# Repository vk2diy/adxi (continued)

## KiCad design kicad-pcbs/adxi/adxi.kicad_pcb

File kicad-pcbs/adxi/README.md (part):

# adxi

## Timeline

 * Conceived: 2024-08-03
 * Designed: 2024-08-03 - 2024-10-10ish
 * Ordered: 2024-10-24
   * Cost: $41.40 for 10 boards + $154.20 for 10 pieces SMT = $195.60 for 10 pieces / 10 = $19.56 each (ex shipping)
   * Note that the ordering was delayed for 2 weeks or something owing to the late stage module design needing revision and wanting to share shipping costs, and this required updates to the [classe2-calculator](https://github.com/vk2diy/classe2-calculator) software.
 * ETA: 2024-11-06 
 * Received: 2024-11-04 (~midday) - total time since ordering ~10-11 days
 * Testing:
   * 2024-11-04: Blew up two boards, discovered USB power issue.
   * 2024-11-05: USB hub, audio and MCU passthru verified with bypass supply. Restored lab to functionality. Worked on a fix, ordered parts.
   * 2024-11-06: Parts received. Testing done manually powering the `TUSB321` chipset and negotiation appears to occur. This suggests a fixable situation. The boost converter still needs debugging.
   * 2024-11-07: Boost converter block instrumentation and testing.
   * 2024-11-08: Plan for potential power stage resolution patch board, scheme for early stage power and failover, benchtop regulator testing.
   * 2024-11-09: Irregular 'regulator free' early stage power solution, new board setup, prepare for firmware programming.
   * 2024-11-24: Test clock generator.

## Initial test

 * Visual inspection
   * No obvious defects
   * The silkscreen now appears to be printed with an inkjet and is much less clear than previous eras
 * Multimeter inspection
   * The GND net appears to be consistent across the board
   * None of the power nets short to GND
 * Assembly test
   * Hard to get the cable through the hole.
   * While easy to thread (dimensions are fine) I failed to account for the solid plug being in the way of the cable
 * Fiddly to tighten nylon nuts around standoffs

## Initial soldering

 * Found pins for MCU not easy to solder, maybe soldermask problem
 * Put one in backwards (oops!)
   * Result: First destroyed board. Nine remain.

## Issue #1: USB-C Power Distribution
 * Next board tried connecting USB-C to a powered USB2 hub just to probe board power
 * See some power on USBC = 0.xV and USBC CLEAN = 0.xV but nothing elsewhere, have to trace back using schematic.
 * Soldered some test leads on to the related test points
 * Configured oscilloscope to view these channels:
   * The scope shows 300mV for CH2 = USBC CLEAN and 500mV for CH1 = USBC
 * Both boards show this issue, which suggests a probable design problem
 * Test results for all three cases (backwards MCU on otherwise new board, no MCU on new board, correct orientation MCU on new board):
   * Test point '5V' = 0V
   * Test point 'USBC' = 500mV
   * Test point 'USBC CLEAN' = 300mV
   * Net 'USB-C-VBUS' = 5V
 * __Conclusion__
   * Design, configuration or placement problem regarding `TUSB321` chipset.
   * Chip is too small to probe directly. but pins are as follows:
     * CC1 = bidirectional USB PD channel
     * CC2 = bidirectional USB PD channel
     * ...
   * __Hypothesis__
     * I misunderstood the datasheet.
       * Instead of the chip relaying the power, which is obtained through the CC channels, it in fact requires a separate supply, which it was not given (and I was treating as an output).
       * Therefore, no power was being relayed to the rest of the board.
       * Additionally, the last page of the datasheet specifies that a 100nF bypass should be present at the VDD pin.
     * The good news is this should be possible to fix without a board revision by bringing VDD power from the 5V verified as present on the `USB-C-VBUS` net, after the ferrite bead.

 * __Attempted fix #1: Jumper cable__
   * Soldered a cable between the `USB-C-VBUS` output after the ferrite and the `USB-C-CLEAN` net (which connects to the `TUSB321` `VDD` pin.
   * __Hypothesis__
     * This should have taken 5V to the 5V clean output as input to the `TUSB321` boost converter, allowing it to negotiate more power.
   * __Result__
     * The `TUSB321` boost converter released magic smoke instantly.
     * Second destroyed board. Eight remain.
   * __Analysis__
     * IC orientation is visually verified as correct
     * Unsure why this occurred, in particular:
       * Given that 5V was measured
       * Given `TUSB321` is supposed to have thermal shutdown
       * Given `TUSB321` only has two inputs, the feedback pin and the main input pin, the latter receiving 5V only
       * Given that the feedback circuit had been modeled.
   * __Conclusion__
     * Design, configuration or placement issue within the `TUB321` circuit
   * __Potential next steps__
     * Use the first destroyed board where this section is intact to test the circuit more carefully using a bench supply and the oscilloscope.
       * This will rely on restoring the test equipment network which appears to be down right now.
       * Very short pulses of power or power with a current cutoff could be measured on the input, output and feedback pins to understand the behaviour without destroying the chip.
       * In the worst case, it should be possible to simply relegate this portion of the circuit to next edition and power the board through the 12V test point.
       * If it appears things are generally in order, then, to reduce inrush current, bulk capacitors could perhaps be disconnected.
     * Bypass the power stage with a direct supply

 * __Attempted bypass #1: Direct 12V supply__
   * Prepared an LXI network configurable power supply Rigol DP832 to connect to 12V test point and GND test point
     * Channel configuration is 12V with overvoltage protection enabled, and 0.05A with overcurrent protection enabled
   * A timed script will enable power for a short time so that the oscilloscope can capture the effect of the power on the other power rails (5V, 3.3V) which should come up.
     * The current limit will be iteratively increased slightly until bring-up succeeds.
     * If these come up, based on the MCU module's internal regulator, then we should be in business, and can move on to testing USB functionality.
     * We may also discover additional problems, although shorts have already been ruled out with multimeter-based continuity probing.
   * Before this test can proceed:
     * I had to debug some issues with my test network due to long period of disuse (network cable had been removed and replaced for another purpose)
     * I had to verify connectivity to the oscilloscope (for screenshot capability) and power supply (for control purposes)
     * It would be good to to first verify the script and control circuit with no load using the multimeter.
   * Configuration screenshot: 
   * Script output: 
```
Tue Nov  5 09:21:44 AM AEDT 2024
DP832 PSU
 - Status: OFF
 - Version: RIGOL TECHNOLOGIES,DP832,DP8C233203778,00.01.16
 - Self test: TopBoard:PASS,BottomBoard:PASS,Fan:PASS

Turning channels off... OK
Setting up channel #1
 - Voltage: 24.000V
 - Voltage limit: 24.000V
 - Voltage limiting: ON
 - Current: 0.500A
 - Current limit: 0.500A
 - Current limiting: ON
Setting up channel #2
 - Voltage: 12.000V
 - Voltage limit: 12.000V
 - Voltage limiting: ON
 - Current: 0.050A
 - Current limit: 0.050A
 - Current limiting: ON
Setting up channel #3
 - Voltage: 5.000V
 - Voltage limit: 5.000V
 - Voltage limiting: ON
 - Current: 0.500A
 - Current limiting: ON

Triggering channel 2 (12V) for test period
 - Enable
Saved screenshot_192.168.8.3_2024-11-05T09:21:44.png
 - Disable

Tue Nov  5 09:21:45 AM AEDT 2024
```

   * Analysis:
     * The screenshot showed no current consumption
     * Connections were therefore checked and an alligator clip was replaced with a soft solder tie-down to the test point
     * The script still ran without change, however re-enabling the channel manually resulted in an overcurrent alarm
     * The current was manually increased as follows: 0.1A, 0.2A
     * At 0.2A power-on occurs and the LED from the MCU can be seen, but this is not reliable.
     * At 0.3A reliability is attained 

```
Tue Nov  5 09:37:42 AM AEDT 2024
DP832 PSU
 - Status: OFF
 - Version: RIGOL TECHNOLOGIES,DP832,DP8C233203778,00.01.16
 - Self test: TopBoard:PASS,BottomBoard:PASS,Fan:PASS

Turning channels off... OK
Setting up channel #1
 - Voltage: 24.000V
 - Voltage limit: 24.000V
 - Voltage limiting: ON
 - Current: 0.500A
 - Current limit: 0.500A
 - Current limiting: ON
Setting up channel #2
 - Voltage: 12.000V
 - Voltage limit: 12.000V
 - Voltage limiting: ON
 - Current: 0.300A
 - Current limit: 0.300A
 - Current limiting: ON
Setting up channel #3
 - Voltage: 5.000V
 - Voltage limit: 5.000V
 - Voltage limiting: ON
 - Current: 0.500A
 - Current limiting: ON

Triggering channel 2 (12V) for test period
 - Enable
Saved screenshot_192.168.8.3_2024-11-05T09:37:43.png
 - Disable

Tue Nov  5 09:37:44 AM AEDT 2024
```

   * Conclusion:
     * Board is at least partly functional with MCU power-on detected
     * Additional channels of 5V and 3.3V also come up as follows  

## USB testing

Now that we have power, it may be possible to test USB connectivity.

Firstly we should take care before plugging in the USB to ensure that the USB VBUS does not burn anything else. The jumper lead that allowed this to burn the boost converter has been removed and the initial state (some minor voltage seen through `TUSB321` `VDD` pin presumably bleeding through from `VBUS_DET` via the large resistor) should be replicated. Since this is insufficient to enable `TUSB321` we should see it remain idle, and the subsequent power stage which burned, namely the jumpered input to the boost converter `MT3608B`, has been removed. Subsequent diodes should prevent further issue.

So the plan is:
 * Plug in USBC
 * See whether anything burns or gets hot
 * If not, then proceed to apply power.
 * After applying power, see if the USB hub comes up, USB audio chipset comes up, or the passthru to the MCU for serial control and programming over the shared USB-C line works.

Here we go... success! `dmesg` output showed the following.

```
[131935.240875] usb 5-4.3: new high-speed USB device number 9 using xhci_hcd
[131935.354394] usb 5-4.3: New USB device found, idVendor=1a40, idProduct=0101,
bcdDevice= 1.00
[131935.354397] usb 5-4.3: New USB device strings: Mfr=0, Product=1, SerialNumbe
r=0
[131935.354399] usb 5-4.3: Product: USB2.0 HUB
[131935.364516] hub 5-4.3:1.0: USB hub found
[131935.364585] hub 5-4.3:1.0: 4 ports detected
[131935.747540] usb 5-4.3.2: new full-speed USB device number 10 using xhci_hcd
[131936.021358] usb 5-4.3.2: New USB device found, idVendor=1a86, idProduct=7523
, bcdDevice= 2.54
[131936.021362] usb 5-4.3.2: New USB device strings: Mfr=0, Product=2, SerialNum
ber=0
[131936.021365] usb 5-4.3.2: Product: USB2.0-Ser!
[131936.360870] usb 5-4.3.1: new full-speed USB device number 11 using xhci_hcd
[131936.635396] usb 5-4.3.1: New USB device found, idVendor=0d8c, idProduct=0012
, bcdDevice= 1.00
[131936.635398] usb 5-4.3.1: New USB device strings: Mfr=1, Product=2, SerialNum
ber=0
[131936.635399] usb 5-4.3.1: Product: USB Audio Device
[131936.635400] usb 5-4.3.1: Manufacturer: C-Media Electronics Inc.
[131936.675747] input: C-Media Electronics Inc. USB Audio Device as /devices/pci
0000:00/0000:00:02.1/0000:03:00.0/0000:04:0c.0/0000:14:00.0/usb5/5-4/5-4.3/5-4.3
.1/5-4.3.1:1.3/0003:0D8C:0012.0009/input/input33
[131936.734251] hid-generic 0003:0D8C:0012.0009: input,hidraw8: USB HID v1.00 De
vice [C-Media Electronics Inc. USB Audio Device] on usb-0000:14:00.0-4.3.1/input
3
[131936.762002] usbcore: registered new interface driver usbserial_generic
[131936.762010] usbserial: USB Serial support registered for generic
[131936.766921] usbcore: registered new interface driver ch341
[131936.766929] usbserial: USB Serial support registered for ch341-uart
[131936.766937] ch341 5-4.3.2:1.0: ch341-uart converter detected
[131936.767494] ch341-uart ttyUSB0: break control not supported, using simulated
 break
[131936.767523] usb 5-4.3.2: ch341-uart converter now attached to ttyUSB0
[131937.067790] usb 5-4.3: USB disconnect, device number 9
[131937.067792] usb 5-4.3.1: USB disconnect, device number 11
[131937.137341] usb 5-4.3.2: USB disconnect, device number 10
[131937.137450] ch341-uart ttyUSB0: ch341-uart converter now disconnected from t
tyUSB0
[131937.137464] ch341 5-4.3.2:1.0: device disconnected
```

This tells us that:
 * USB data lines work both on the host-side and the board-side
 * The USB hub works
 * The audio chipset is detected
 * The USB cable passthru to the MCU module works
   * The CH341 serial UART on the MCU is detected

Fantastic! Let's power it on a bit longer to get a USB tree display.

```
        |__ Port 003: Dev 015, If 0, Class=Hub, Driver=hub/4p, 480M
            |__ Port 001: Dev 017, If 0, Class=Audio, Driver=snd-usb-audio, 12M
            |__ Port 001: Dev 017, If 1, Class=Audio, Driver=snd-usb-audio, 12M
            |__ Port 001: Dev 017, If 2, Class=Audio, Driver=snd-usb-audio, 12M
            |__ Port 001: Dev 017, If 3, Class=Human Interface Device, Driver=usbhid, 12M
            |__ Port 002: Dev 016, If 0, Class=Vendor Specific Class, Driver=ch341, 12M
```

Great. 

Here we can see four device interfaces on the audio chipset, three audio and one USB HID (used for microphone buttons).

The audio devices are used to receive audio from and send audio to the transceiver.

The final device is the MCU module's CH341 serial UART interface which is used for serial control and programming.

## Next steps

A reasonable step might now be to __attempt to program the device__ in order to better verify on-board functionality.

Alternatively, we could __go back and try to solve the USB C power distribution issue__.  Let's do that as it's annoying me that we've been so lucky with the later-stage USB devices but failed with the base power.

## Back to the USB power distribution problem

It seems that what may have happened is that I misunderstood the USB-C power distribution system, as it is my first time designing both USB devices and USBC powered devices.

Basically, there are three logical lines related to power on the USB C standard:
 * The `VBUS` line, which is the USB bus voltage. This goes all the way back to USB 1.0.
 * The `CC1` and `CC2` lines, which are new to USB-C and used for the negotiation of more power.

It seems that my wrong-headed design-time assumption was that the power would be negotiated on *and distributed on* the `CC1` and `CC2` lines, because `VBUS` has far too many backwards compatibility issues to be brought up to a high voltage and amperage.

However, it seems this assumption was wrong, and that in fact the `VBUS` line is used for the power distribution and the `CC1` and `CC2` lines are only used for power negotiation. This is odd to me, but I suppose that's how it is, because it would explain our situation as follows:
 * The `TUSB321` chip never comes up
 * The `TUSB321` documentation final page suggests adding a 100nF bypass cap on the `VDD` pin (implying external power input required through this pin)
 * The direct connection between `VBUS` and the boost converter fried it, because:
   * After `VDD` was powered on for `TUSB321` (since it's on the same net that was directly powered), it negotiated more power which was in excess of the boost converter `MT3608B` `IN` pin's absolute maximum voltage.

This is a sketchy comprehension but seems like it may be heading in the right direction.

If that holds, and we could probably do some further testing to verify the theory, then:
 * In terms of safely bringing up the TUSB321 using only USB power, we could perhaps cut the connection from VDD to the `MT3608B` and instead connect it to pin 5 (`VBUS_DET`) which lies behind a protective 909K resistor which the `TUSB321` datasheet states is for reducing modern high VBUS voltages to a safe small level. Presumably this power level may be adequate for powering the chip.
 * The `TUSB321` datasheet says that it should be functional at 4.5V, that all pins have an absolute maximum of 6-6.3V, and that the threshold voltage should be 4V
 * We should perhaps go back to re-measure the threshold voltage presented before and after the 909K resistor, however I believe the voltage is well below 1V and thus insufficient.

Some potential fixes:
 * Some __parallel, alternate resistor configuration__ to obtain a higher voltage (eg. 200K instead of 909K)
 * A __5V regulator__ capable of the higher voltages that may be presented on the `VBUS` line
   * Most regulators seem to fail around 17V (AMS1117)
   * I found a local supply of 35V 1.5A capable 5V regulators, L7805CV, and procured them. They should arrive tomorrow.
 * A __12V regulator__ to reduce the `VBUS` line (if higher than 5V) down to 12V stable, instead of the current boost converter

## The Plan

 * Cut the connection between the `TUSB321` and the `MT3608B`.
 * Wire a 5V regulator output or a resistor setup to the `TUSB321` chip's `VDD` pin.
 * Instrument `CC1`, `CC2`, `VDD` and the USB `VBUS` line.
 * Run a power-up test capturing oscilloscope output to verify that `TUSB321` is now powering up correctly, and what effect this has if any on the `VBUS` line voltage.
 * Then, move on to `MT3608B` subsystem testing based on the newly clarified and verified context.
   * If, as suspected, the `TUSB321` negotiates changes to the `VBUS` line that present a voltage higher than desired for the `MT3608B`, use a 12V regulator module instead.
   * If, after verifying power-up, the `TUSB321` negotiates changes to the `VBUS` line that only present a higher amperage, further consideration will be required.

## Regulator insertion

It seems this test point is the correct place to target: solderable, large, out of the way.

However, before executing that plan it may be beneficial to first use the bench supply with a low current set just to see what happens when voltage is applied.

### Bench supply pre-test

The first step was removing the `MT3608B` boost converter which had anyway blown up. After failing with the soldering iron I succeeded with the hot air gun, while holding the part with tweezers and applying horizontal pressure to dislodge it. This effectively isolates the `VDD` pin of the `TUSB321` so that the 'USBC CLEAN' test point can be used to feed it a specific and precise current from the bench supply.

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
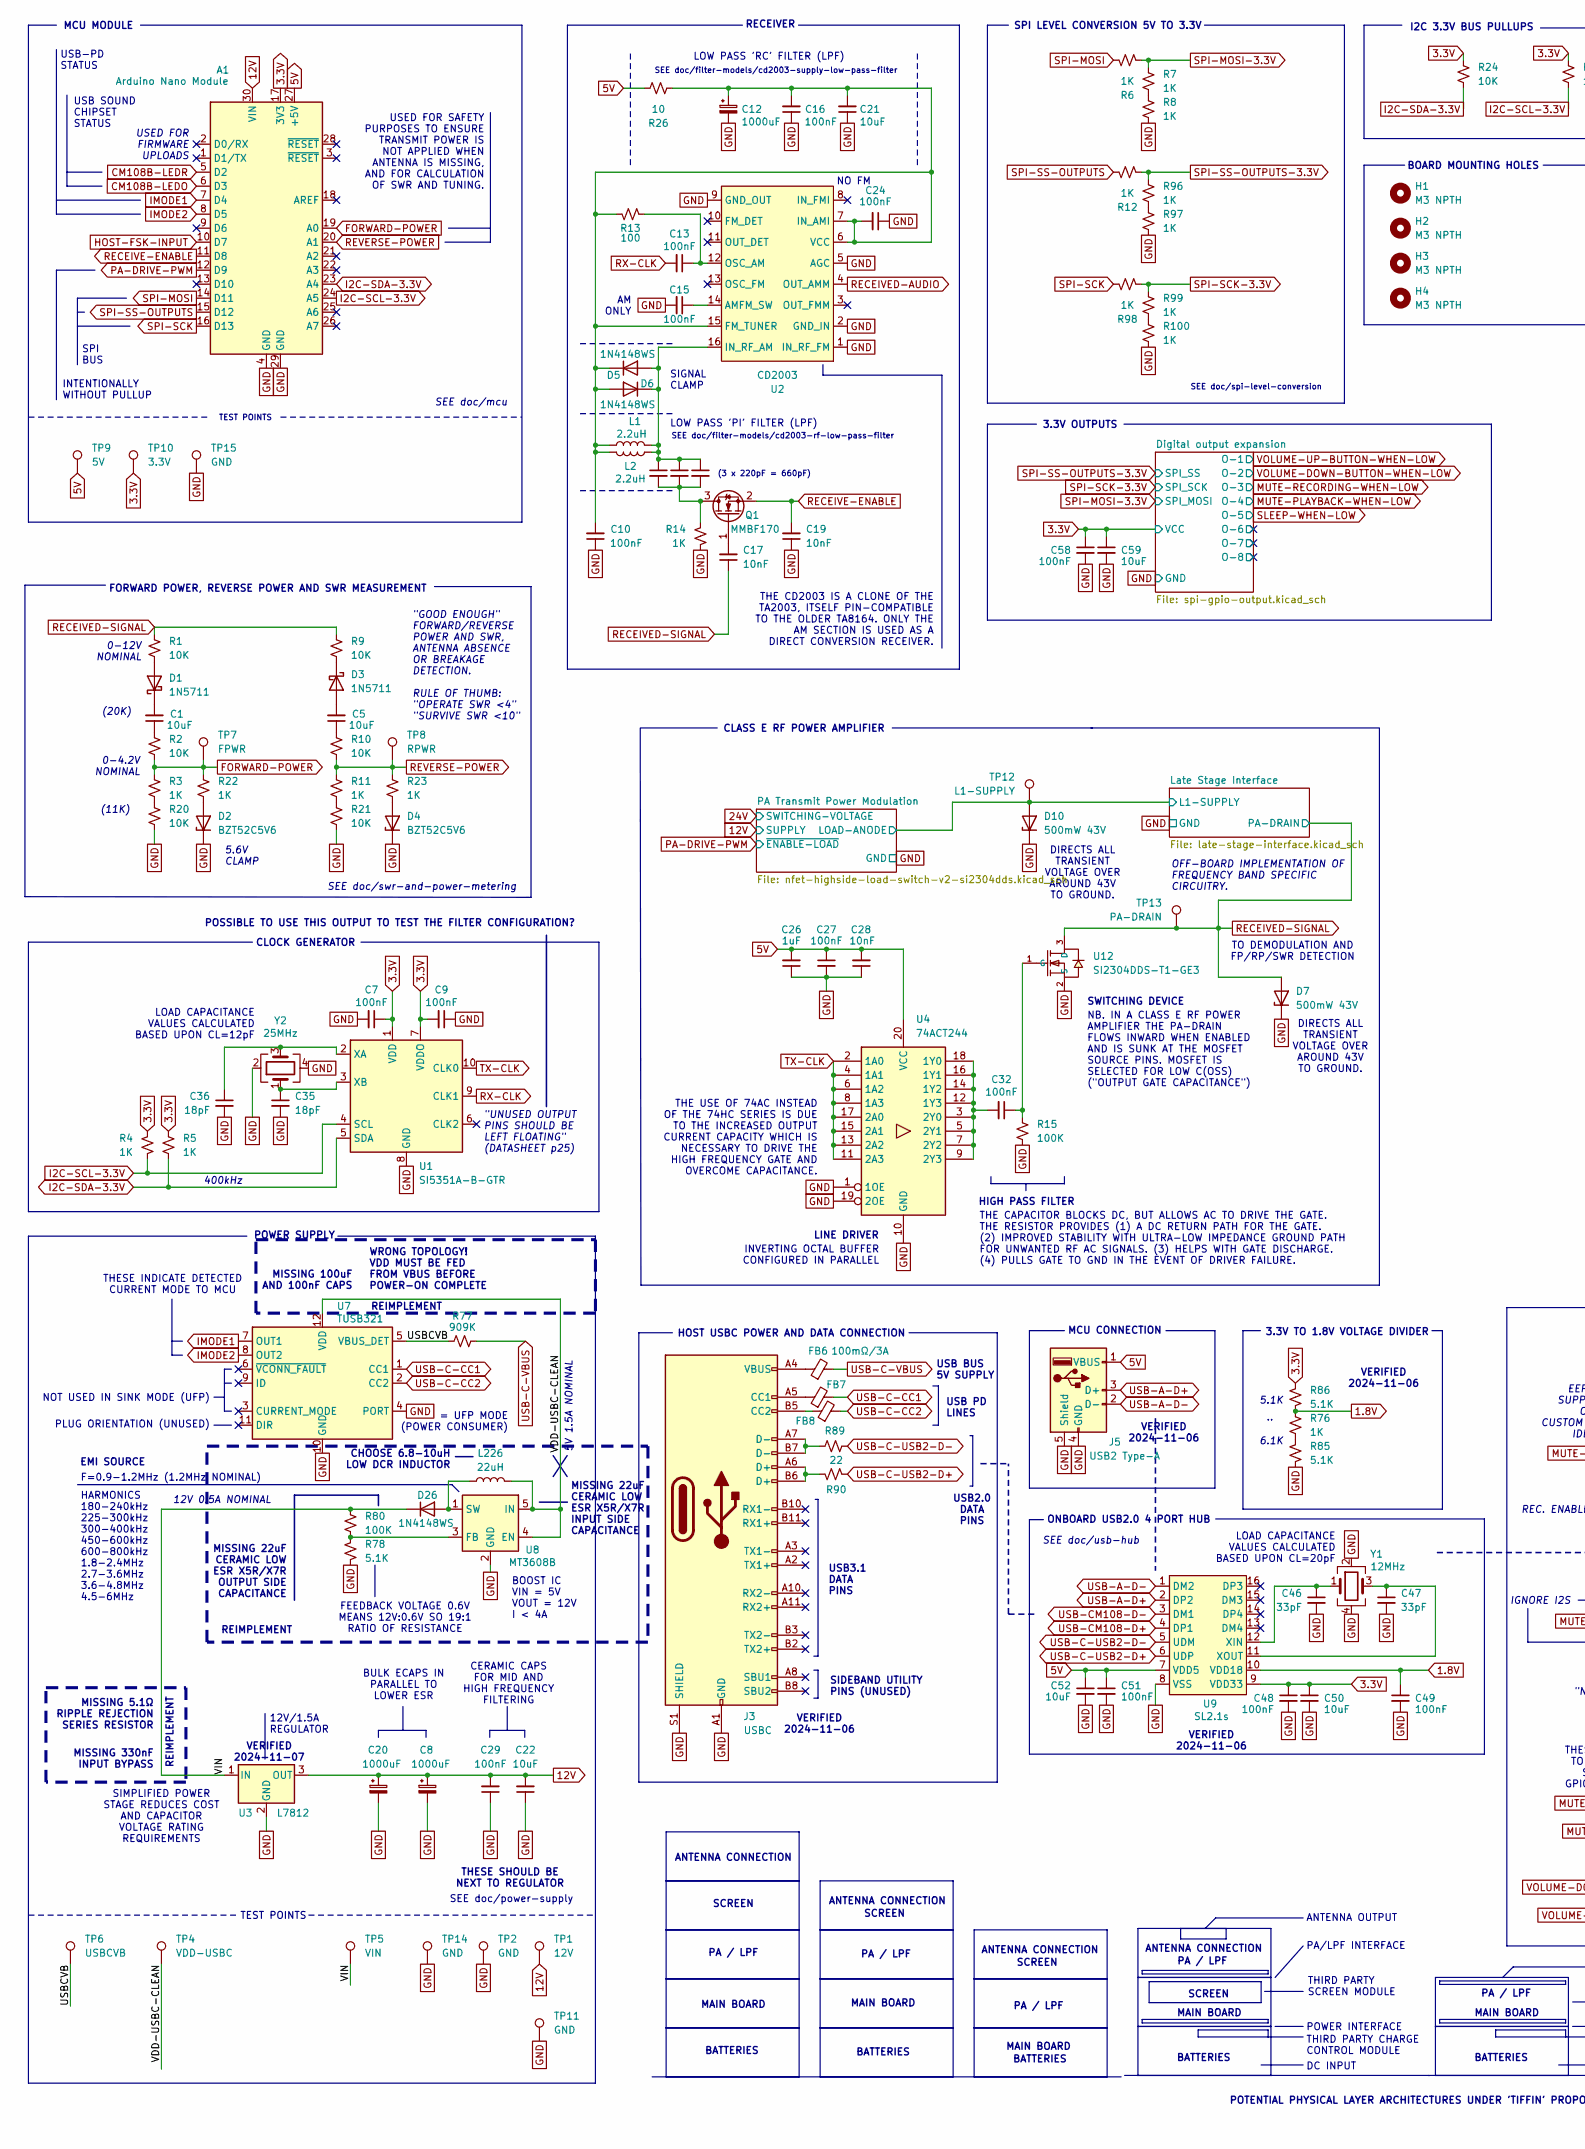
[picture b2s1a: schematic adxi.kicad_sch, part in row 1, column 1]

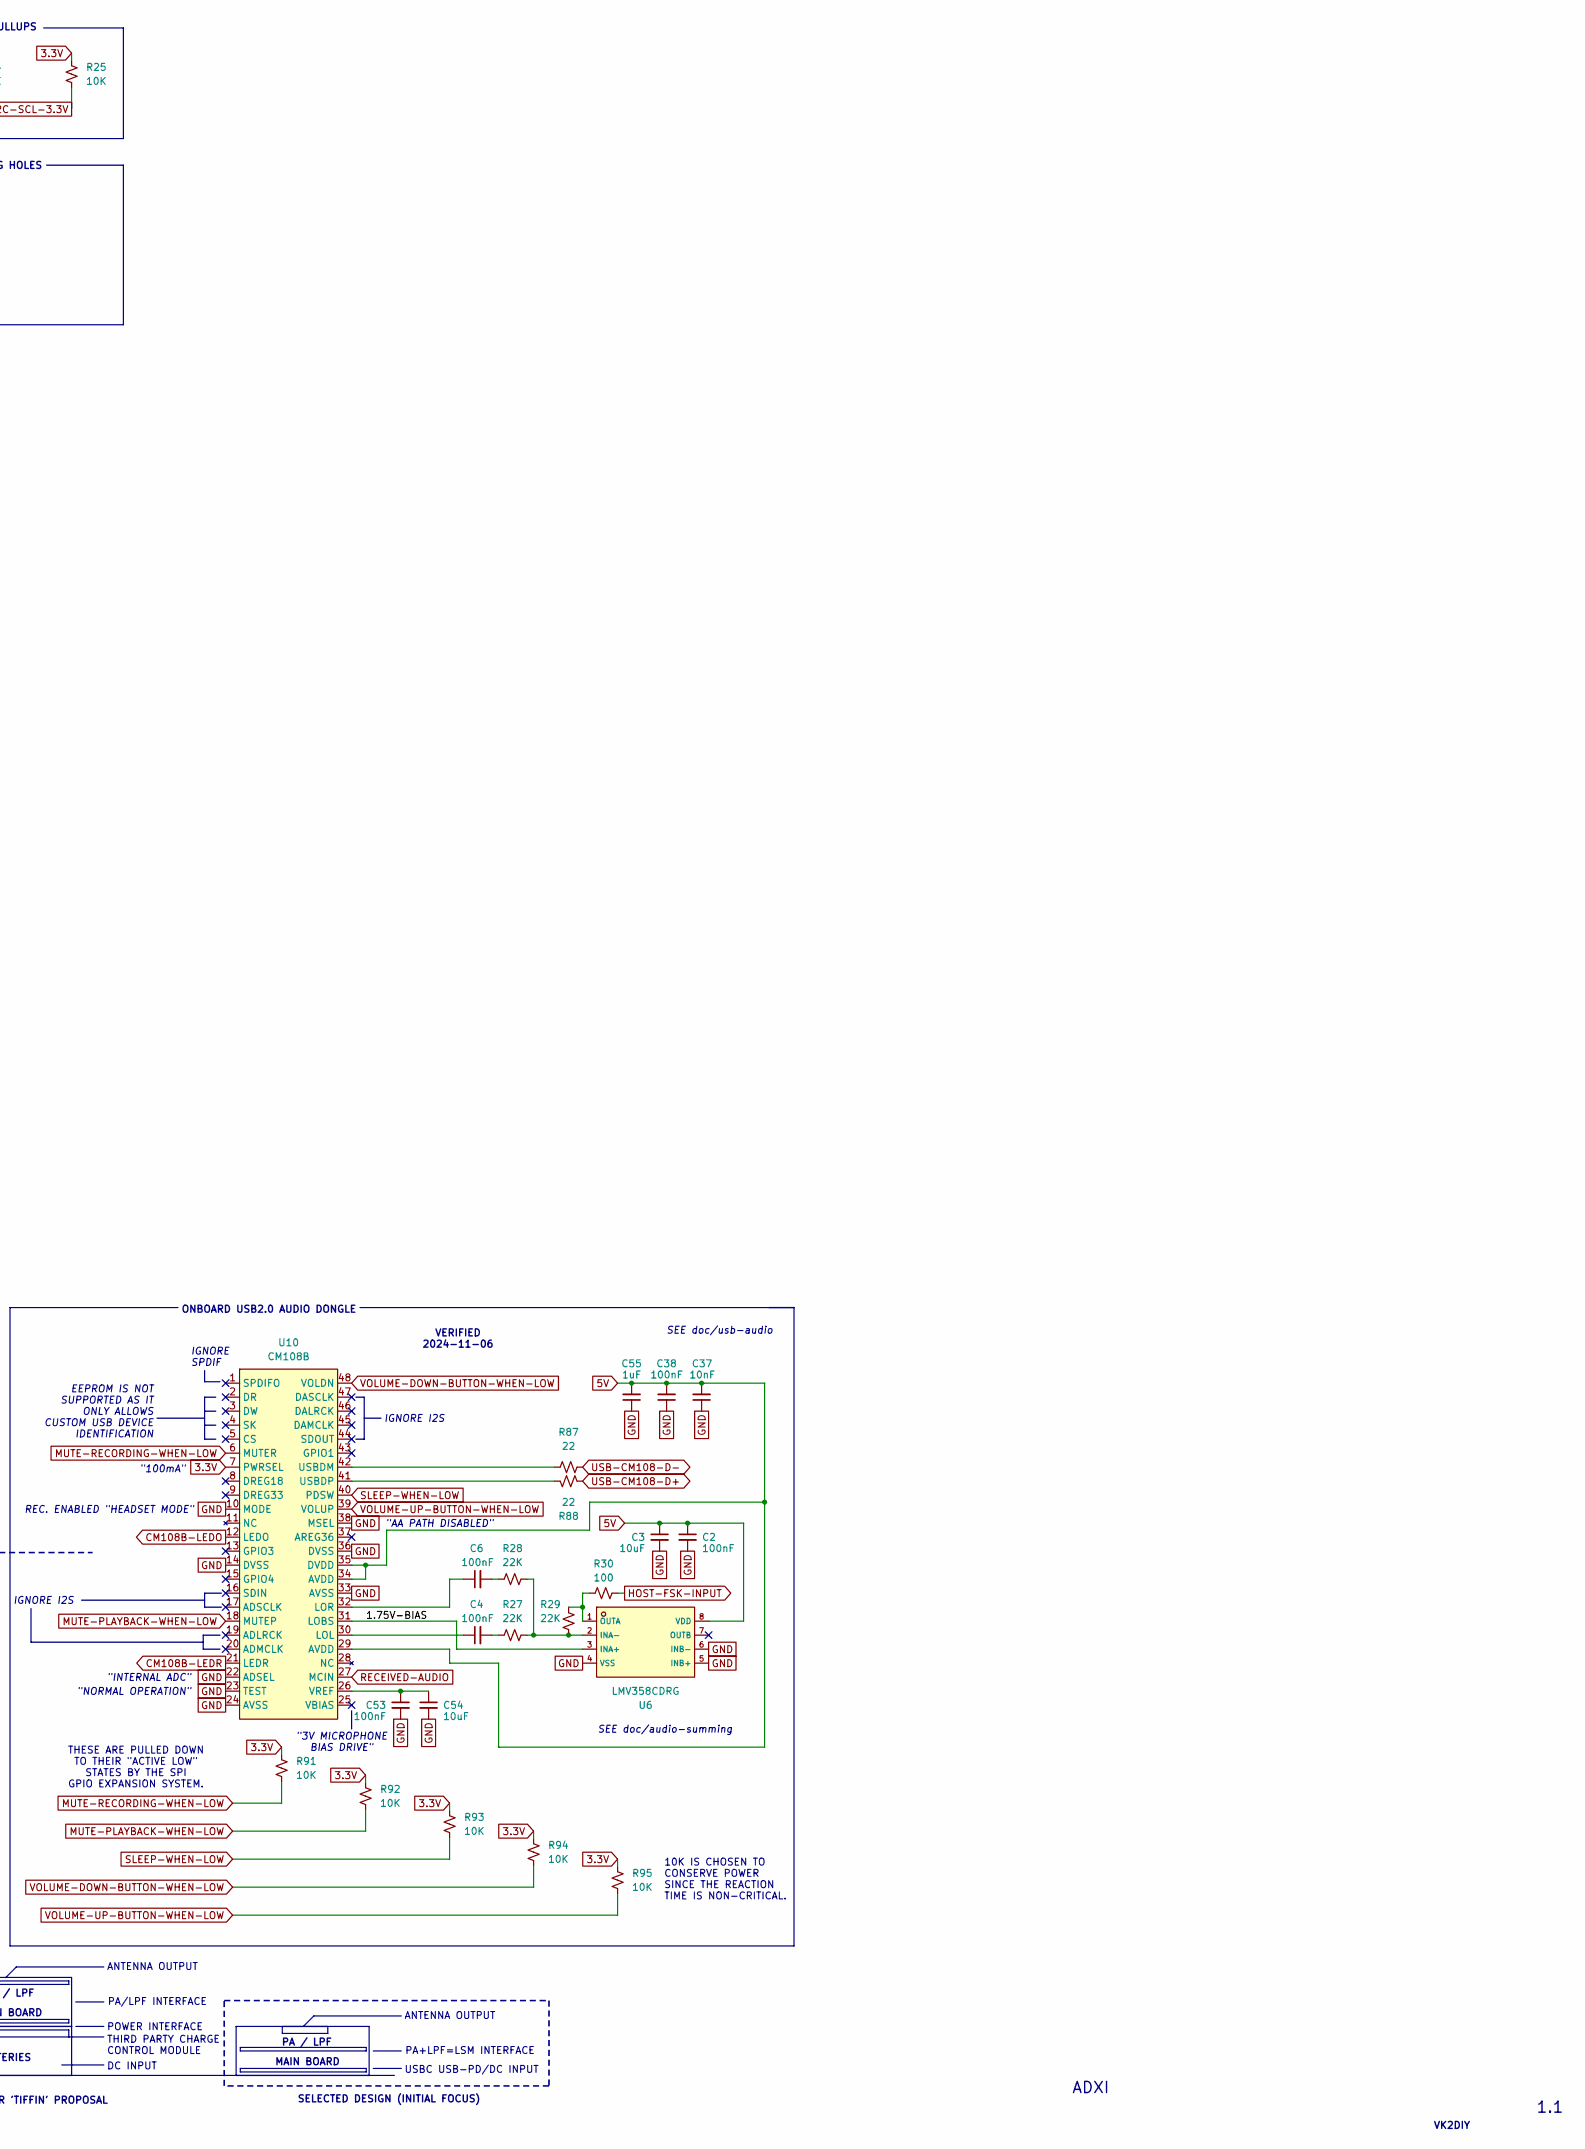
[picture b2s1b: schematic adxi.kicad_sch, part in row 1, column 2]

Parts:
A1: Arduino Nano Module; Arduino_Nano
C1, C5: 10uF; C_1210_3225Metric; MPN FS32X106K101EGG; LCSC Part # C5156756
C2, C4, C6, C27, C48, C49, C51, C53, C58: 100nF; C_0603_1608Metric; MPN CC0603KRX7R9BB104; LCSC Part # C14663
C3, C50, C52, C54, C59: 10uF; C_0603_1608Metric; MPN CL10A106KP8NNNC; LCSC Part # C19702
C7, C9, C10, C13, C15, C16, C24, C29, C32, C38: 100nF; C_0805_2012Metric; MPN CL21B104KCFNNNE; LCSC Part # C28233
C8, C12, C20: 1000uF; C_Elec_10x10.2; MPN RVT1C102M1010; LCSC Part # C3359
C11, C39, C40: 220pF; C_0603_1608Metric; MPN CL10B221KB8NNNC; LCSC Part # C1603
C17, C19, C28, C37: 10nF; C_0603_1608Metric; MPN 0603B103K500NT; LCSC Part # C57112
C21, C22: 10uF; C_1206_3216Metric; MPN CL31A106KBHNNNE; LCSC Part # C13585
C26, C55: 1uF; C_0603_1608Metric; MPN CL10A105KB8NNNC; LCSC Part # C15849
C35, C36: 18pF; C_0402_1005Metric; MPN 0402CG180J500NT; LCSC Part # C1549
C46, C47: 33pF; C_0603_1608Metric; MPN CL10C330JB8NNNC; LCSC Part # C1663
D1, D3: 1N5711; D_SOD-123; MPN 1N5711W-7-F; LCSC Part # C154843
D2, D4: BZT52C5V6; D_SOD-123; MPN BZT52C5V6; LCSC Part # C173406
D5, D6, D26: 1N4148WS; D_SOD-323; MPN 1N4148WS; LCSC Part # C2128
D7, D10: 500mW 43V; D_SOD-123; MPN MMSZ5260B; LCSC Part # C268628
FB6, FB7, FB8: 100mΩ/3A; C_1206_3216Metric; MPN CBW321609U800T; LCSC Part # C130273
H1, H2, H3, H4: M3 NPTH; MountingHole_3.2mm_M3_DIN965
J3: USBC; TYPE-C-SMD_C9900025773; MPN TYPE-C 24P QT 143; LCSC Part # C5156605
J5: USB2 Type-A; USB-A-SMD_10.0-QTJ6.3; MPN 10.0 QTJ6.3; LCSC Part # C404966
L1, L2: 2.2uH; L_1008_2520Metric; MPN WPN252012H2R2MT; LCSC Part # C98350
L226: 22uH; L_Changjiang_FNR4030S; MPN FNR4030S220MT; LCSC Part # C167883
Q1: MMBF170; SOT-23; MPN MMBF170; LCSC Part # C130879
R1, R2, R9, R10, R20, R21: 10K; R_1206_3216Metric; MPN 1206W4F1002T5E; LCSC Part # C17902
R3, R4, R5, R11, R14, R22, R23, R76: 1K; R_1206_3216Metric; MPN 1206W4F1001T5E; LCSC Part # C4410
R6, R7, R8, R12, R96, R97, R98, R99, R100: 1K; R_0603_1608Metric; MPN 0603WAF1001T5E; LCSC Part # C21190
R13: 100; R_1206_3216Metric; MPN 1206W4F1000T5E; LCSC Part # C17901
R15, R80: 100K; R_1206_3216Metric; MPN 1206W4F1003T5E; LCSC Part # C17900
R24, R25, R91, R92, R93, R94, R95: 10K; R_0402_1005Metric; MPN 0402WGF1002TCE; LCSC Part # C25744
R26: 10; R_1206_3216Metric; MPN 1206W4F100JT5E; LCSC Part # C17903
R27, R28, R29: 22K; R_0805_2012Metric; MPN 0805W8F2202T5E; LCSC Part # C17560
R30: 100; R_0805_2012Metric; MPN 0805W8F1000T5E; LCSC Part # C17408
R77: 909K; R_1206_3216Metric; MPN RS-06K9093FT; LCSC Part # C323176
R78, R85, R86: 5.1K; R_0805_2012Metric; MPN 0805W8F5101T5E; LCSC Part # C27834
R87, R88, R89, R90: 22; R_0805_2012Metric; MPN 0805W8F220JT5E; LCSC Part # C17561
TP1: 12V; TestPoint_THTPad_2.0x2.0mm_Drill1.0mm
TP2, TP11, TP14, TP15: GND; TestPoint_THTPad_2.0x2.0mm_Drill1.0mm
TP4: VDD-USBC; TestPoint_THTPad_2.0x2.0mm_Drill1.0mm
TP5: VIN; TestPoint_THTPad_2.0x2.0mm_Drill1.0mm
TP6: USBCVB; TestPoint_THTPad_2.0x2.0mm_Drill1.0mm
TP7: FPWR; TestPoint_THTPad_2.0x2.0mm_Drill1.0mm
TP8: RPWR; TestPoint_THTPad_2.0x2.0mm_Drill1.0mm
TP9: 5V; TestPoint_THTPad_2.0x2.0mm_Drill1.0mm
TP10: 3.3V; TestPoint_THTPad_2.0x2.0mm_Drill1.0mm
TP12: L1-SUPPLY; TestPoint_THTPad_2.0x2.0mm_Drill1.0mm
TP13: PA-DRAIN; TestPoint_THTPad_2.0x2.0mm_Drill1.0mm
U1: SI5351A-B-GTR; MSOP-10_3x3mm_P0.5mm; MPN SI5351A-B-GTR; LCSC Part # C504891
U2: CD2003; SOP-16_3.9x9.9mm_P1.27mm; MPN CD2003GB/GP; LCSC Part # C7421626
U3: L7812; TO-263-2; MPN L7812CDTR(XBLW); LCSC Part # C22357877
U4: 74ACT244; TSSOP-20_4.4x6.5mm_P0.65mm; MPN SN74ACT244PWR; LCSC Part # C6930
U6: LMV358CDRG; SOIC-8_L4.9-W3.9-P1.27-LS6.0-TL; MPN LMV358CDRG; LCSC Part # C2977080
U7: TUSB321; Texas_X2QFN-12_1.6x1.6mm_P0.4mm; MPN TUSB321RWBR; LCSC Part # C139392
U8: MT3608B; SOT-23-6; MPN MT3608B; LCSC Part # C19189893
U9: SL2.1s; SSOP-16_L4.6-W2.6-P0.53-LS4.0-BL; MPN SL2.1s; LCSC Part # C2684433
U10: CM108B; LQFP-48_7x7mm_P0.5mm; MPN CM108B; LCSC Part # C371347
U12: SI2304DDS-T1-GE3; SOT-23-3_L2.9-W1.6-P1.90-LS2.8-BR; MPN SI2304DDS-T1-GE3; LCSC Part # C56372
Y1: 12MHz; Crystal_SMD_3225-4Pin_3.2x2.5mm; MPN X322512MSB4SI; LCSC Part # C9002
Y2: 25MHz; Crystal_SMD_3225-4Pin_3.2x2.5mm; MPN X322525MOB4SI; LCSC Part # C9006

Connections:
1.8V: C49.1, R76.1, R86.2, U9.10 (VDD18)
3.3V: A1.17 (3V3), C7.1, C9.2, C48.1, C50.1, C58.1, C59.1, R4.1, R5.1, R24.1, R25.1, R86.1, R91.1, R92.1, R93.1, R94.1, R95.1, TP10.1, U1.1 (VDD), U1.7 (VDDO), U9.9 (VDD33), U10.7 (PWRSEL); also elsewhere on the board
5V: A1.27 (+5V), C2.1, C3.1, C26.2, C27.1, C28.2, C37.2, C38.2, C51.1, C52.1, C55.2, J5.1 (VBUS), R26.1, TP9.1, U4.20 (VCC), U6.8 (VDD), U9.7 (VDD5), U10.29 (AVDD), U10.34 (AVDD), U10.35 (DVDD)
12V: A1.30 (VIN), C8.1, C20.1, C22.2, C29.2, TP1.1, U3.3 (OUT); also elsewhere on the board
/1.75V-BIAS: U6.3 (INA+), U10.31 (LOBS)
/Late Stage Interface/L1-SUPPLY: D10.2 (A), TP12.1; also elsewhere on the board
/USBCVB: R77.2, TP6.1, U7.5 (VBUS_DET)
/VDD-USBC-CLEAN: L226.2, TP4.1, U7.12 (VDD), U8.4 (EN), U8.5 (IN)
/VIN: D26.1 (K), R80.2, TP5.1, U3.1 (IN)
CM108B-LEDO: A1.6 (D3), U10.12 (LEDO)
CM108B-LEDR: A1.5 (D2), U10.21 (LEDR)
FORWARD-POWER: A1.19 (A0), R2.1, R3.1, R22.1, TP7.1
GND: A1.4 (GND), A1.29 (GND), C2.2, C3.2, C7.2, C8.2, C9.1, C10.1, C12.2, C15.2, C16.1, C19.1, C20.2, C21.1, C22.1, C24.1, C26.1, C27.2, C28.1, C29.1, C35.2, C36.2, C37.1, C38.1, C46.2, C47.2, C48.2, C49.2, C50.2, C51.2, C52.2, C53.2, C54.2, C55.1, C58.2, C59.2, D2.1 (K), D4.1 (K), D7.1 (K), D10.1 (K), J3.A1 (GND), J3.A12 (GND), J3.B1 (GND), J3.B12 (GND), J3.S1 (SHIELD), J5.4 (GND), J5.5 (Shield), R8.1, R14.2, R15.1, R20.1, R21.1, R78.2, R85.2, R97.1, R100.1, TP2.1, TP11.1, TP14.1, TP15.1, U1.8 (GND), U2.1 (IN_RF_FM), U2.2 (GND_IN), U2.5 (AGC), U2.9 (GND_OUT), U3.2 (GND), U4.1 (1OE), U4.10 (GND), U4.19 (2OE), U6.4 (VSS), U6.5 (INB+), U6.6 (INB-), U7.4 (PORT), U7.10 (GND), U8.2 (GND), U9.8 (VSS), U10.10 (MODE), U10.14 (DVSS), U10.22 (ADSEL), U10.23 (TEST), U10.24 (AVSS), U10.33 (AVSS), U10.36 (DVSS), U10.38 (MSEL), U12.2 (S), Y1.2, Y1.4, Y2.2, Y2.4; also elsewhere on the board
HOST-FSK-INPUT: A1.10 (D7), R30.2
I2C-SCL-3.3V: A1.24 (A5), R4.2, R25.2, U1.4 (SCL)
I2C-SDA-3.3V: A1.23 (A4), R5.2, R24.2, U1.5 (SDA)
IMODE1: A1.7 (D4), U7.7 (OUT1)
IMODE2: A1.8 (D5), U7.8 (OUT2)
MUTE-PLAYBACK-WHEN-LOW: R92.2, U10.18 (MUTEP); also elsewhere on the board
MUTE-RECORDING-WHEN-LOW: R91.2, U10.6 (MUTER); also elsewhere on the board
unnamed: C1.1, R2.2
unnamed: C4.2, R27.1
unnamed: C5.1, R10.2
unnamed: C6.2, R28.1
unnamed: D1.2 (A), R1.1
unnamed: C1.2, D1.1 (K)
unnamed: D2.2 (A), R22.2
unnamed: C5.2, D3.2 (A)
unnamed: D3.1 (K), R9.1
unnamed: D4.2 (A), R23.2
unnamed: C11.1, C39.1, C40.1, D5.2 (A), D6.1 (K), L1.2, L2.1, U2.16 (IN_RF_AM)
unnamed: C10.2, C12.1, C16.2, C21.2, C24.2, D5.1 (K), D6.2 (A), L1.1, L2.2, R13.2, R26.2, U2.6 (VCC), U2.7 (IN_AMI), U2.15 (FM_TUNER)
unnamed: D26.2 (A), L226.1, U8.1 (SW)
unnamed: FB6.1, J3.A4 (VBUS), J3.A9 (VBUS), J3.B4 (VBUS), J3.B9 (VBUS)
unnamed: FB7.1, J3.A5 (CC1)
unnamed: FB8.1, J3.B5 (CC2)
unnamed: J3.A6 (D+), J3.B6 (D+), R90.1
unnamed: J3.A7 (D-), J3.B7 (D-), R89.1
unnamed: C11.2, C39.2, C40.2, Q1.3 (D), R14.1
unnamed: C17.2, Q1.1 (G)
unnamed: R7.1, R8.2
unnamed: R11.2, R21.2
unnamed: R3.2, R20.2
unnamed: R76.2, R85.1
unnamed: R96.1, R97.2
unnamed: R99.1, R100.2
unnamed: C36.1, U1.2 (XA), Y2.3
unnamed: C35.1, U1.3 (XB), Y2.1
unnamed: C15.1, U2.14 (AMFM_SW)
unnamed: C13.1, R13.1, U2.12 (OSC_AM)
unnamed: C32.2, U4.3 (2Y0), U4.5 (2Y1), U4.7 (2Y2), U4.9 (2Y3), U4.12 (1Y3), U4.14 (1Y2), U4.16 (1Y1), U4.18 (1Y0)
unnamed: R27.2, R28.2, R29.1, U6.2 (INA-)
unnamed: R29.2, R30.1, U6.1 (OUTA)
unnamed: R78.1, R80.1, U8.3 (FB)
unnamed: C46.1, U9.12 (XIN), Y1.1
unnamed: C47.1, U9.11 (XOUT), Y1.3
unnamed: C4.1, U10.30 (LOL)
unnamed: C6.1, U10.32 (LOR)
unnamed: R87.1, U10.42 (USBDM)
unnamed: R88.1, U10.41 (USBDP)
unnamed: C53.1, C54.1, U10.26 (VREF)
unnamed: C32.1, R15.2, U12.1 (G)
PA-DRIVE-PWM: A1.12 (D9); also elsewhere on the board
RECEIVE-ENABLE: A1.11 (D8), C19.2, Q1.2 (S)
RECEIVED-AUDIO: U2.4 (OUT_AMM), U10.27 (MCIN)
RECEIVED-SIGNAL: C17.1, D7.2 (A), R1.2, R9.2, TP13.1, U12.3 (D); also elsewhere on the board
REVERSE-POWER: A1.20 (A1), R10.1, R11.1, R23.1, TP8.1
RX-CLK: C13.2, U1.9 (CLK1)
SLEEP-WHEN-LOW: R93.2, U10.40 (PDSW); also elsewhere on the board
SPI-MOSI: A1.14 (D11), R6.1
SPI-MOSI-3.3V: R6.2, R7.2; also elsewhere on the board
SPI-SCK: A1.16 (D13), R98.1
SPI-SCK-3.3V: R98.2, R99.2; also elsewhere on the board
SPI-SS-OUTPUTS: A1.15 (D12), R12.1
SPI-SS-OUTPUTS-3.3V: R12.2, R96.2; also elsewhere on the board
TX-CLK: U1.10 (CLK0), U4.2 (1A0), U4.4 (1A1), U4.6 (1A2), U4.8 (1A3), U4.11 (2A3), U4.13 (2A2), U4.15 (2A1), U4.17 (2A0)
USB-A-D+: J5.3 (D+), U9.2 (DP2)
USB-A-D-: J5.2 (D-), U9.1 (DM2)
USB-C-CC1: FB7.2, U7.1 (CC1)
USB-C-CC2: FB8.2, U7.2 (CC2)
USB-C-USB2-D+: R90.2, U9.6 (UDP)
USB-C-USB2-D-: R89.2, U9.5 (UDM)
USB-C-VBUS: FB6.2, R77.1
USB-CM108-D+: R88.2, U9.4 (DP1)
USB-CM108-D-: R87.2, U9.3 (DM1)
VOLUME-DOWN-BUTTON-WHEN-LOW: R94.2, U10.48 (VOLDN); also elsewhere on the board
VOLUME-UP-BUTTON-WHEN-LOW: R95.2, U10.39 (VOLUP); also elsewhere on the board

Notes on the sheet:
HIGH PASS FILTER
SIDEBAND UTILITY PINS (UNUSED)
BATTERIES
"AA PATH DISABLED"
"3V MICROPHONE BIAS DRIVE"
LINE DRIVER
REIMPLEMENT
FEEDBACK VOLTAGE 0.6V MEANS 12V:0.6V SO 19:1 RATIO OF RESISTANCE
I2C 3.3V BUS PULLUPS
0-4.2V NOMINAL
THE CAPACITOR BLOCKS DC, BUT ALLOWS AC TO DRIVE THE GATE. THE RESISTOR PROVIDES (1) A DC RETURN PATH FOR THE GATE. (2) IMPROVED STABILITY WITH ULTRA-LOW IMPEDANCE GROUND PATH FOR UNWANTED RF AC SIGNALS. (3) HELPS WITH GATE DISCHARGE. (4) PULLS GATE TO GND IN THE EVENT OF DRIVER FAILURE.
VERIFIED 2024-11-06
MAIN BOARD
0-12V NOMINAL
POWER INTERFACE
SCREEN
VK2DIY
THESE INDICATE DETECTED CURRENT MODE TO MCU
NB. IN A CLASS E RF POWER AMPLIFIER THE PA-DRAIN FLOWS INWARD WHEN ENABLED AND IS SUNK AT THE MOSFET SOURCE PINS. MOSFET IS SELECTED FOR LOW C(OSS) ("OUTPUT GATE CAPACITANCE")
12V/1.5A REGULATOR
AM ONLY
5.6V CLAMP
3.3V TO 1.8V VOLTAGE DIVIDER
WRONG TOPOLOGY! VDD MUST BE FED FROM VBUS BEFORE POWER-ON COMPLETE
REC. ENABLED "HEADSET MODE"
PLUG ORIENTATION (UNUSED)
CERAMIC CAPS FOR MID AND HIGH FREQUENCY FILTERING
MCU MODULE
HARMONICS 180-240kHz 225-300kHz 300-400kHz 450-600kHz 600-800kHz 1.8-2.4MHz 2.7-3.6MHz 3.6-4.8MHz 4.5-6MHz
(3 x 220pF = 660pF)
5V 1.5A NOMINAL
USED FOR SAFETY PURPOSES TO ENSURE TRANSMIT POWER IS NOT APPLIED WHEN ANTENNA IS MISSING, AND FOR CALCULATION OF SWR AND TUNING.
SPI BUS
BOARD MOUNTING HOLES
USBC USB-PD/DC INPUT
SEE doc/filter-models/cd2003-rf-low-pass-filter
USB BUS 5V SUPPLY
PA / LPF
THE CD2003 IS A CLONE OF THE TA2003, ITSELF PIN-COMPATIBLE TO THE OLDER TA8164. ONLY THE AM SECTION IS USED AS A DIRECT CONVERSION RECEIVER.
OFF-BOARD IMPLEMENTATION OF FREQUENCY BAND SPECIFIC CIRCUITRY.

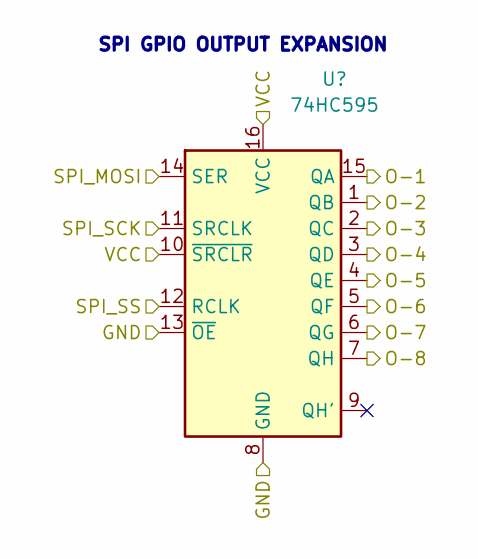
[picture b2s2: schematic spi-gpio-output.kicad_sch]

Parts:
U5: 74HC595; SOIC-16_3.9x9.9mm_P1.27mm; MPN 74HC595D,118; LCSC Part # C5947

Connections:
3.3V: U5.10 (~SRCLR), U5.16 (VCC); also elsewhere on the board
/Digital output expansion/O-6: U5.5 (QF)
/Digital output expansion/O-7: U5.6 (QG)
/Digital output expansion/O-8: U5.7 (QH)
GND: U5.8 (GND), U5.13 (~OE); also elsewhere on the board
MUTE-PLAYBACK-WHEN-LOW: U5.3 (QD); also elsewhere on the board
MUTE-RECORDING-WHEN-LOW: U5.2 (QC); also elsewhere on the board
SLEEP-WHEN-LOW: U5.4 (QE); also elsewhere on the board
SPI-MOSI-3.3V: U5.14 (SER); also elsewhere on the board
SPI-SCK-3.3V: U5.11 (SRCLK); also elsewhere on the board
SPI-SS-OUTPUTS-3.3V: U5.12 (RCLK); also elsewhere on the board
VOLUME-DOWN-BUTTON-WHEN-LOW: U5.1 (QB); also elsewhere on the board
VOLUME-UP-BUTTON-WHEN-LOW: U5.15 (QA); also elsewhere on the board

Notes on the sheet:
SPI GPIO OUTPUT EXPANSION

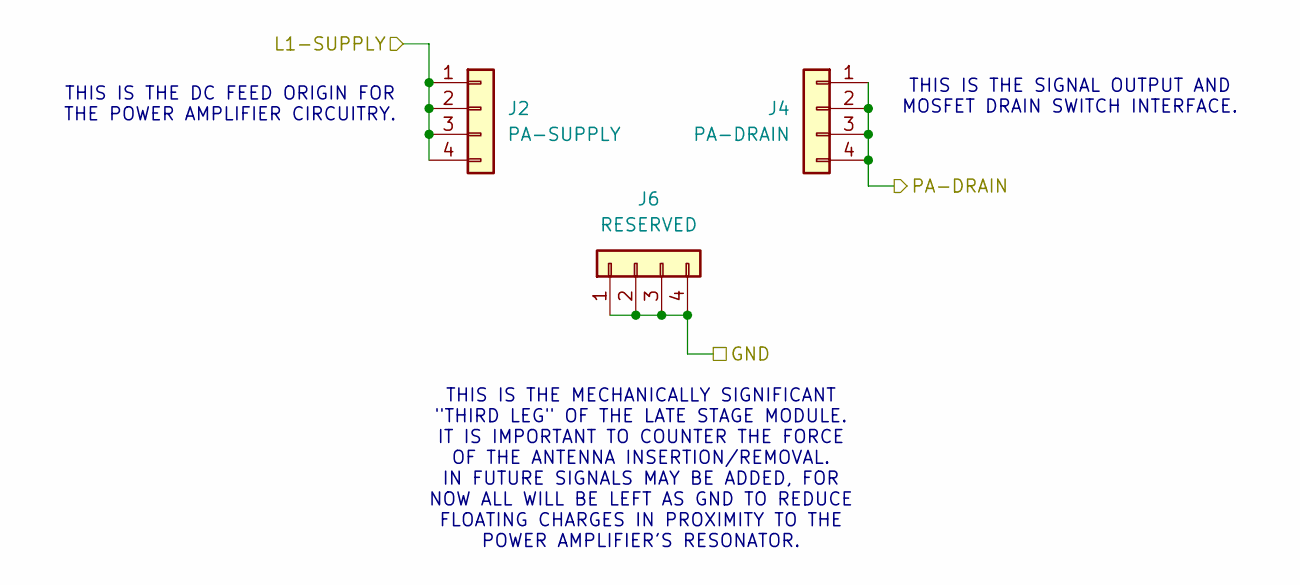
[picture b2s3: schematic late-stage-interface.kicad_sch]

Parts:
J2: PA-SUPPLY; PinHeader_1x04_P2.54mm_Vertical
J4: PA-DRAIN; PinHeader_1x04_P2.54mm_Vertical
J6: RESERVED; PinHeader_1x04_P2.54mm_Vertical

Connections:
/Late Stage Interface/L1-SUPPLY: J2.1, J2.2, J2.3, J2.4; also elsewhere on the board
GND: J6.1, J6.2, J6.3, J6.4; also elsewhere on the board
RECEIVED-SIGNAL: J4.1, J4.2, J4.3, J4.4; also elsewhere on the board

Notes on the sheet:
THIS IS THE DC FEED ORIGIN FOR THE POWER AMPLIFIER CIRCUITRY.
THIS IS THE MECHANICALLY SIGNIFICANT "THIRD LEG" OF THE LATE STAGE MODULE. IT IS IMPORTANT TO COUNTER THE FORCE OF THE ANTENNA INSERTION/REMOVAL. IN FUTURE SIGNALS MAY BE ADDED, FOR NOW ALL WILL BE LEFT AS GND TO REDUCE FLOATING CHARGES IN PROXIMITY TO THE POWER AMPLIFIER'S RESONATOR.
THIS IS THE SIGNAL OUTPUT AND MOSFET DRAIN SWITCH INTERFACE.

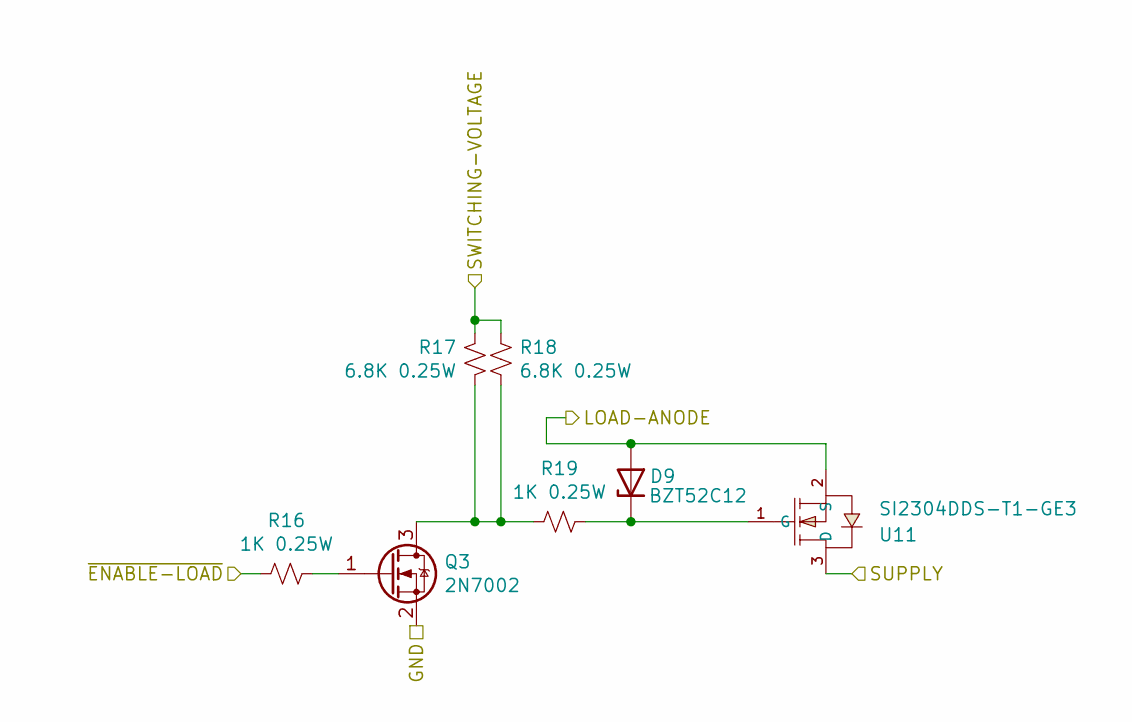
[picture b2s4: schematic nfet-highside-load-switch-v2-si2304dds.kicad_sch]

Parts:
D9: BZT52C12; D_SOD-123; MPN BZT52C12; LCSC Part # C173429
Q3: 2N7002; SOT-23; MPN 2N7002; LCSC Part # C8545
R16, R19: 1K 0.25W; R_1206_3216Metric; MPN 1206W4F1001T5; LCSC Part # C4410
R17, R18: 6.8K 0.25W; R_1206_3216Metric; MPN 1206W4F6801T5E; LCSC Part # C26034
U11: SI2304DDS-T1-GE3; SOT-23-3_L2.9-W1.6-P1.90-LS2.8-BR; MPN SI2304DDS-T1-GE3; LCSC Part # C56372

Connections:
12V: U11.3 (D); also elsewhere on the board
24V: R17.2, R18.2
/Late Stage Interface/L1-SUPPLY: D9.2 (A), U11.2 (S); also elsewhere on the board
GND: Q3.2 (S); also elsewhere on the board
unnamed: D9.1 (K), R19.1, U11.1 (G)
unnamed: Q3.3 (D), R17.1, R18.1, R19.2
unnamed: Q3.1 (G), R16.1
PA-DRIVE-PWM: R16.2; also elsewhere on the board

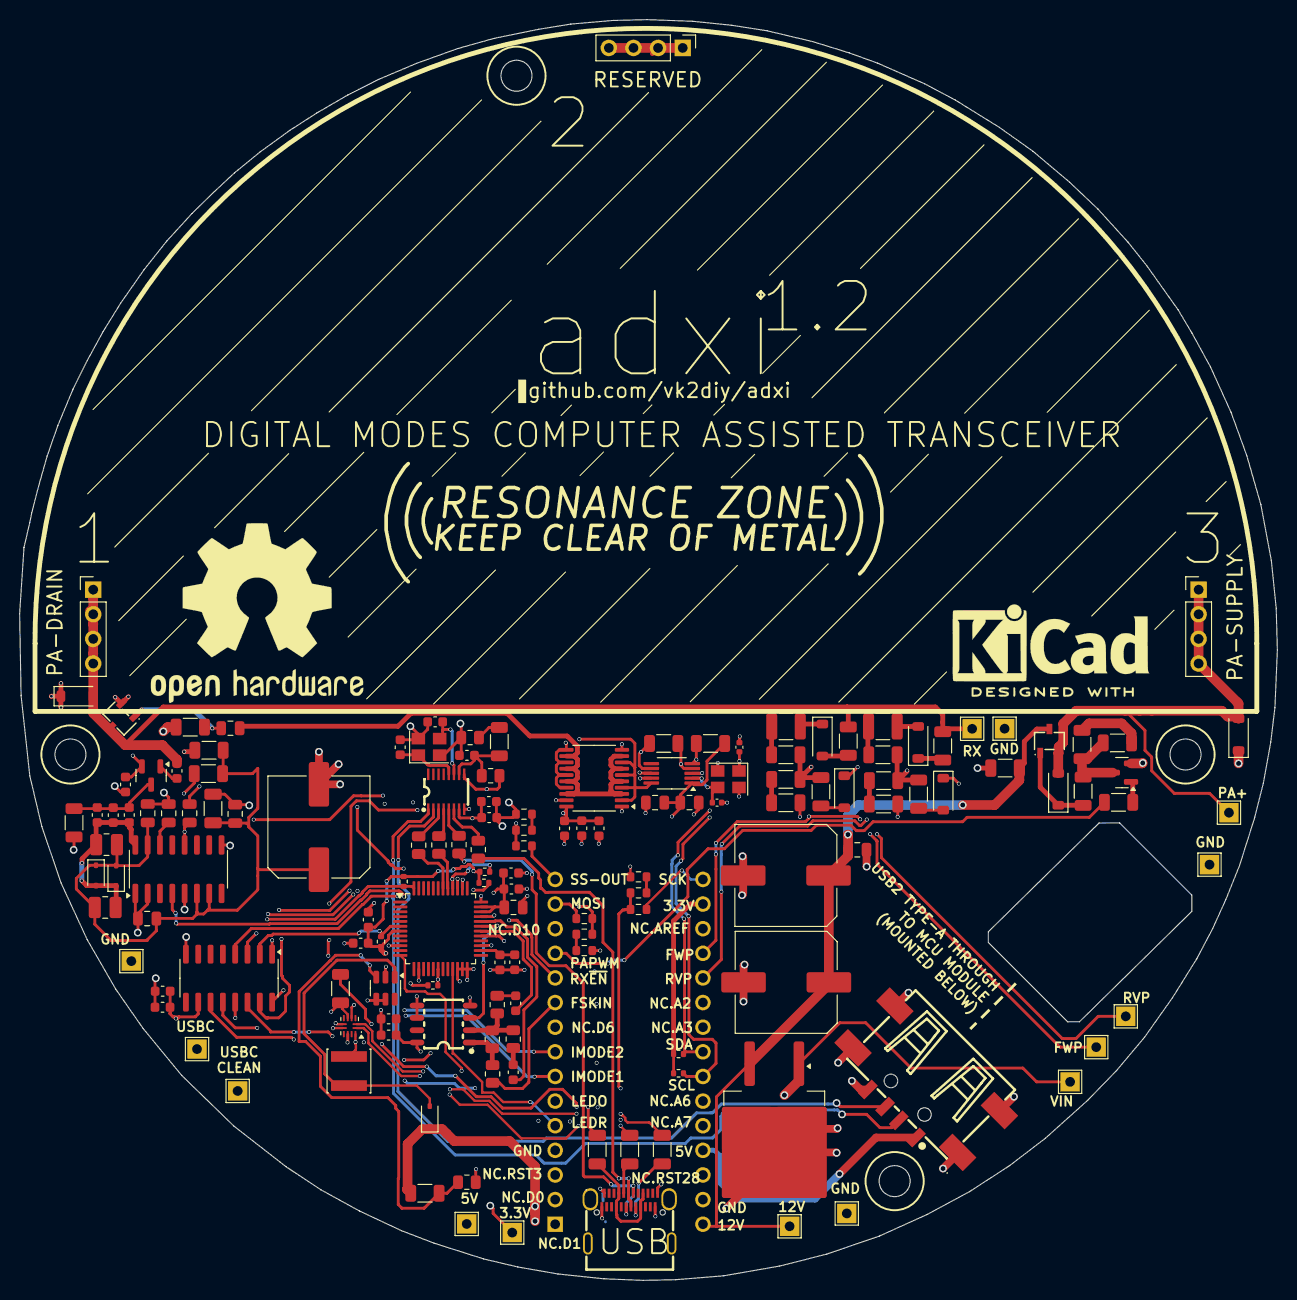
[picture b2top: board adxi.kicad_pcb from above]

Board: 4 copper layers, 129.7 x 130.0 mm, 150 parts (1 on the bottom side), 91 nets.
